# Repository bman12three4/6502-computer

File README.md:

# 65C02 Computer

My very own 65C02 computer.

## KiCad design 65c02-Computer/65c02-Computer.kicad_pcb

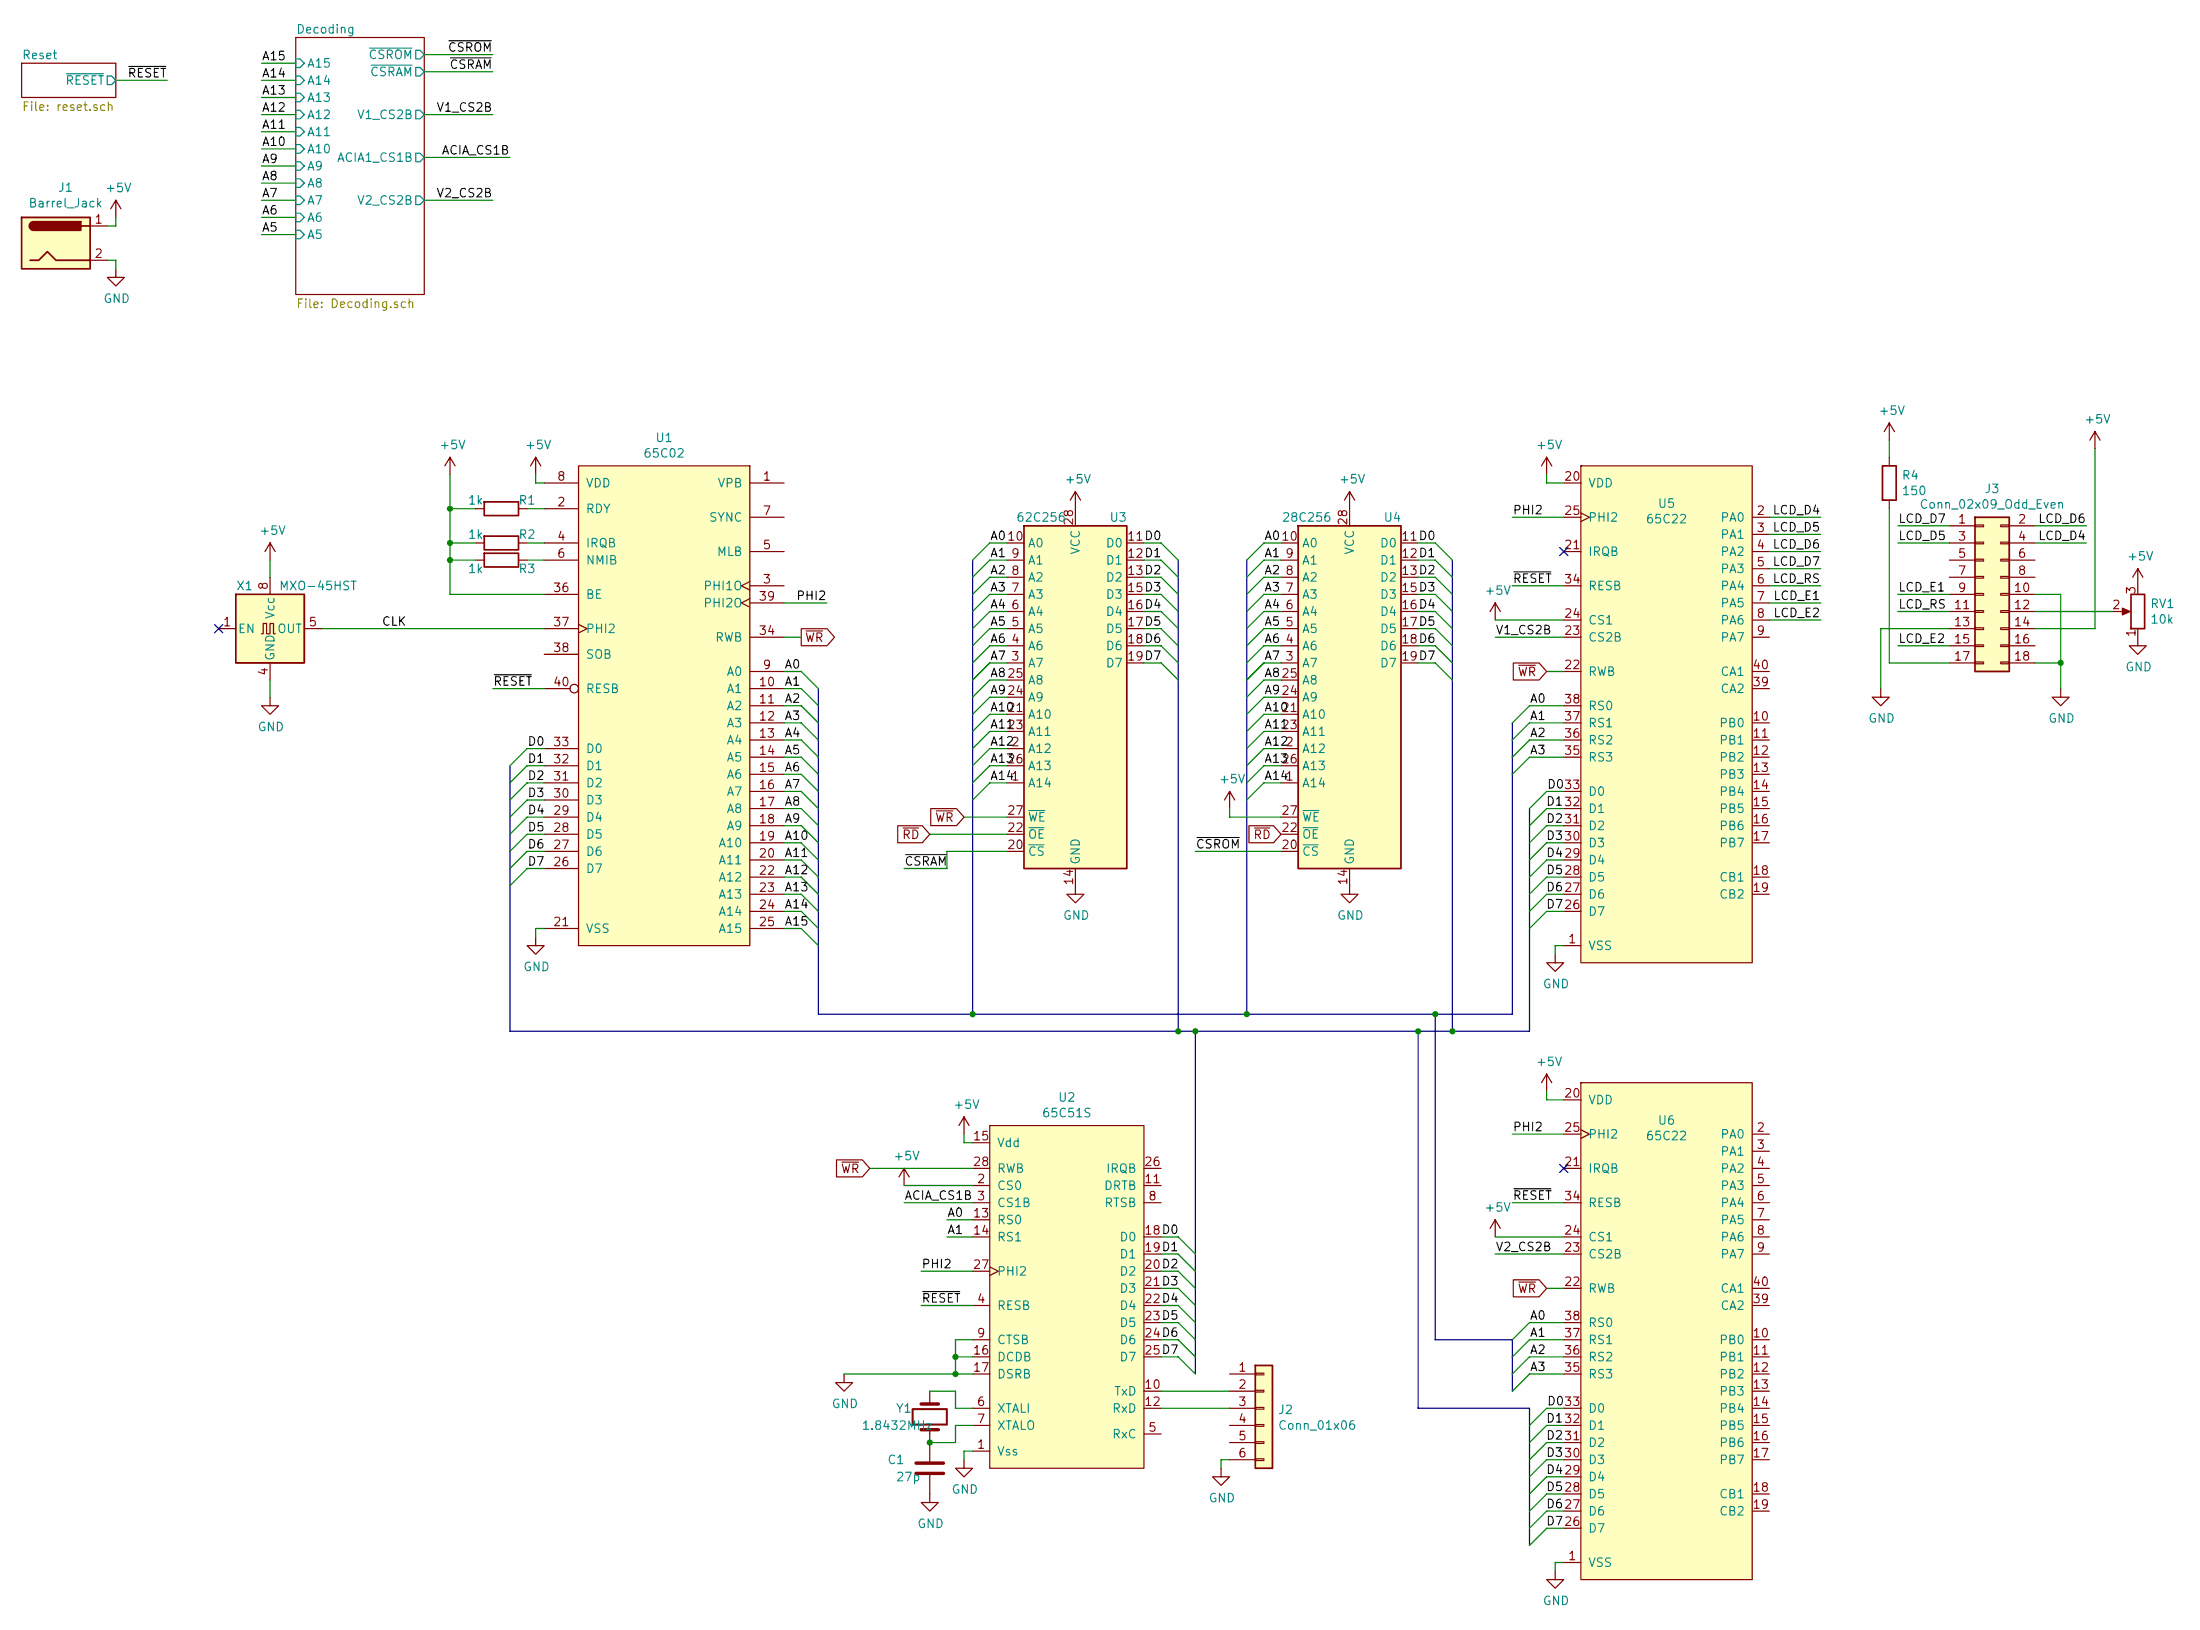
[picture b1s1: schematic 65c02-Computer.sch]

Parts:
C1: 27p; C_Disc_D3.8mm_W2.6mm_P2.50mm
J1: Barrel_Jack; BarrelJack_CUI_PJ-102AH_Horizontal
J2: Conn_01x06; PinSocket_1x06_P2.54mm_Horizontal
J3: Conn_02x09_Odd_Even; PinHeader_2x09_P2.54mm_Vertical
R1, R2, R3: 1k; R_Axial_DIN0207_L6.3mm_D2.5mm_P10.16mm_Horizontal
R4: 150; R_Axial_DIN0207_L6.3mm_D2.5mm_P10.16mm_Horizontal
RV1: 10k; PinHeader_1x03_P2.54mm_Vertical
U1: 65C02; DIP-40_W15.24mm_Socket_LongPads
U2: 65C51S; DIP-28_W15.24mm_Socket_LongPads
U3: 62C256; DIP-28_W15.24mm_Socket_LongPads
U4: 28C256; DIP-28_W15.24mm_Socket_LongPads
U5, U6: 65C22; DIP-40_W15.24mm_Socket_LongPads
X1: MXO-45HST; Oscillator_DIP-8
Y1: 1.8432MHz; Crystal_HC49-U_Vertical

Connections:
+5V: J1.1, J3.14, R1.2, R2.2, R3.2, R4.1, RV1.3, U1.8 (VDD), U1.36 (BE), U2.2 (CS0), U2.15 (Vdd), U3.28 (VCC), U4.27 (~WE), U4.28 (VCC), U5.20 (VDD), U5.24 (CS1), U6.20 (VDD), U6.24 (CS1), X1.8 (Vcc); also elsewhere on the board
/A0: U1.9 (A0), U2.13 (RS0), U3.10 (A0), U4.10 (A0), U5.38 (RS0), U6.38 (RS0)
/A1: U1.10 (A1), U2.14 (RS1), U3.9 (A1), U4.9 (A1), U5.37 (RS1), U6.37 (RS1)
/A2: U1.11 (A2), U3.8 (A2), U4.8 (A2), U5.36 (RS2), U6.36 (RS2)
/A3: U1.12 (A3), U3.7 (A3), U4.7 (A3), U5.35 (RS3), U6.35 (RS3)
/A4: U1.13 (A4), U3.6 (A4), U4.6 (A4)
/A5: U1.14 (A5), U3.5 (A5), U4.5 (A5); also elsewhere on the board
/A6: U1.15 (A6), U3.4 (A6), U4.4 (A6); also elsewhere on the board
/A7: U1.16 (A7), U3.3 (A7), U4.3 (A7); also elsewhere on the board
/A8: U1.17 (A8), U3.25 (A8), U4.25 (A8); also elsewhere on the board
/A9: U1.18 (A9), U3.24 (A9), U4.24 (A9); also elsewhere on the board
/A10: U1.19 (A10), U3.21 (A10), U4.21 (A10); also elsewhere on the board
/A11: U1.20 (A11), U3.23 (A11), U4.23 (A11); also elsewhere on the board
/A12: U1.22 (A12), U3.2 (A12), U4.2 (A12); also elsewhere on the board
/A13: U1.23 (A13), U3.26 (A13), U4.26 (A13); also elsewhere on the board
/A14: U1.24 (A14), U3.1 (A14), U4.1 (A14); also elsewhere on the board
/A15: U1.25 (A15), U3.20 (~CS); also elsewhere on the board
/ACIA_CS1B: U2.3 (CS1B); also elsewhere on the board
/CLK: U1.37 (PHI2), X1.5 (OUT)
/D0: U1.33 (D0), U2.18 (D0), U3.11 (D0), U4.11 (D0), U5.33 (D0), U6.33 (D0)
/D1: U1.32 (D1), U2.19 (D1), U3.12 (D1), U4.12 (D1), U5.32 (D1), U6.32 (D1)
/D2: U1.31 (D2), U2.20 (D2), U3.13 (D2), U4.13 (D2), U5.31 (D2), U6.31 (D2)
/D3: U1.30 (D3), U2.21 (D3), U3.15 (D3), U4.15 (D3), U5.30 (D3), U6.30 (D3)
/D4: U1.29 (D4), U2.22 (D4), U3.16 (D4), U4.16 (D4), U5.29 (D4), U6.29 (D4)
/D5: U1.28 (D5), U2.23 (D5), U3.17 (D5), U4.17 (D5), U5.28 (D5), U6.28 (D5)
/D6: U1.27 (D6), U2.24 (D6), U3.18 (D6), U4.18 (D6), U5.27 (D6), U6.27 (D6)
/D7: U1.26 (D7), U2.25 (D7), U3.19 (D7), U4.19 (D7), U5.26 (D7), U6.26 (D7)
/LCD_D4: J3.4, U5.2 (PA0)
/LCD_D5: J3.3, U5.3 (PA1)
/LCD_D6: J3.2, U5.4 (PA2)
/LCD_D7: J3.1, U5.5 (PA3)
/LCD_E1: J3.9, U5.7 (PA5)
/LCD_E2: J3.15, U5.8 (PA6)
/LCD_RS: J3.11, U5.6 (PA4)
/PHI2: U1.39 (PHI2O), U2.27 (PHI2), U5.25 (PHI2), U6.25 (PHI2)
/V1_CS2B: U5.23 (CS2B); also elsewhere on the board
/V2_CS2B: U6.23 (CS2B); also elsewhere on the board
/~CSROM: U4.20 (~CS); also elsewhere on the board
/~RESET: U1.40 (RESB), U2.4 (RESB), U5.34 (RESB), U6.34 (RESB); also elsewhere on the board
GND: C1.2, J1.2, J2.6, J3.10, J3.13, J3.18, RV1.1, U1.21 (VSS), U2.1 (Vss), U2.9 (CTSB), U2.16 (DCDB), U2.17 (DSRB), U3.14 (GND), U4.14 (GND), U5.1 (VSS), U6.1 (VSS), X1.4 (GND); also elsewhere on the board
unnamed: C1.1, U2.7 (XTALO), Y1.1
unnamed: J2.2, U2.10 (TxD)
unnamed: J2.3, U2.12 (RxD)
unnamed: J3.12, RV1.2
unnamed: J3.17, R4.2
unnamed: R1.1, U1.2 (RDY)
unnamed: R2.1, U1.4 (IRQB)
unnamed: R3.1, U1.6 (NMIB)
unnamed: U2.6 (XTALI), Y1.2
~RD: U3.22 (~OE), U4.22 (~OE); also elsewhere on the board
~WR: U1.34 (RWB), U2.28 (RWB), U3.27 (~WE), U5.22 (RWB), U6.22 (RWB); also elsewhere on the board

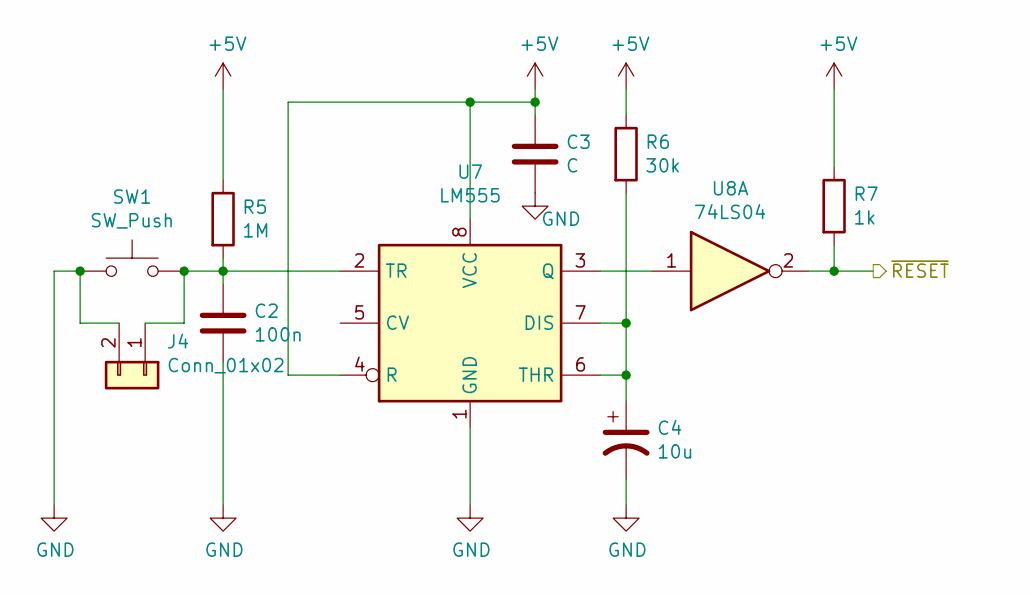
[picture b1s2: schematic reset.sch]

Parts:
C2: 100n; C_Disc_D3.8mm_W2.6mm_P2.50mm
C3: C; C_Disc_D3.8mm_W2.6mm_P2.50mm
C4: 10u; CP_Radial_D8.0mm_P5.00mm
J4: Conn_01x02; PinHeader_1x02_P2.54mm_Vertical
R5: 1M; R_Axial_DIN0207_L6.3mm_D2.5mm_P10.16mm_Horizontal
R6: 30k; R_Axial_DIN0207_L6.3mm_D2.5mm_P10.16mm_Horizontal
R7: 1k; R_Axial_DIN0207_L6.3mm_D2.5mm_P10.16mm_Horizontal
SW1: SW_Push; SW_PUSH_6mm_H4.3mm
U7: LM555; DIP-8_W7.62mm
U8: 74LS04; DIP-14_W7.62mm

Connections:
+5V: C3.1, R5.1, R6.1, R7.1, U7.4 (R), U7.8 (VCC); also elsewhere on the board
/~RESET: R7.2, U8.2; also elsewhere on the board
GND: C2.2, C3.2, C4.2, J4.2, SW1.1, U7.1 (GND); also elsewhere on the board
unnamed: C2.1, J4.1, R5.2, SW1.2, U7.2 (TR)
unnamed: C4.1, R6.2, U7.6 (THR), U7.7 (DIS)
unnamed: U7.3 (Q), U8.1

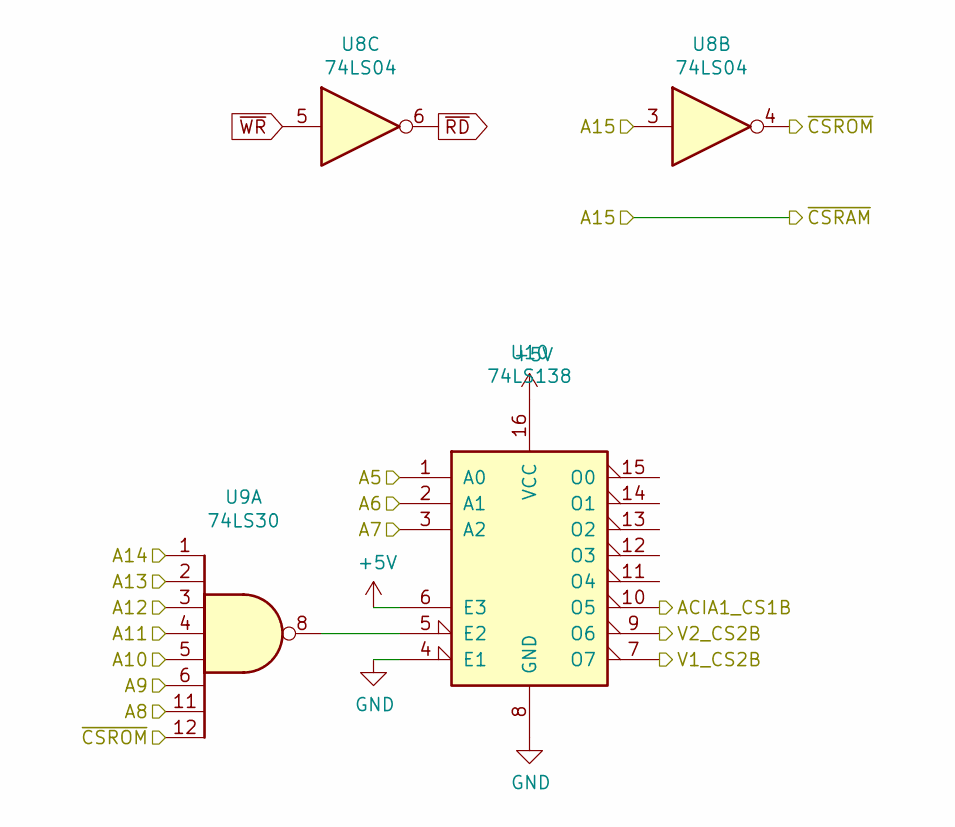
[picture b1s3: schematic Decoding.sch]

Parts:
U8: 74LS04; DIP-14_W7.62mm
U9: 74LS30; DIP-14_W7.62mm_LongPads
U10: 74LS138; DIP-16_W7.62mm_LongPads

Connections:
+5V: U10.6 (E3), U10.16 (VCC); also elsewhere on the board
/A5: U10.1 (A0); also elsewhere on the board
/A6: U10.2 (A1); also elsewhere on the board
/A7: U10.3 (A2); also elsewhere on the board
/A8: U9.11; also elsewhere on the board
/A9: U9.6; also elsewhere on the board
/A10: U9.5; also elsewhere on the board
/A11: U9.4; also elsewhere on the board
/A12: U9.3; also elsewhere on the board
/A13: U9.2; also elsewhere on the board
/A14: U9.1; also elsewhere on the board
/A15: U8.3; also elsewhere on the board
/ACIA_CS1B: U10.10 (O5); also elsewhere on the board
/V1_CS2B: U10.7 (O7); also elsewhere on the board
/V2_CS2B: U10.9 (O6); also elsewhere on the board
/~CSROM: U8.4, U9.12; also elsewhere on the board
GND: U10.4 (E1), U10.8 (GND); also elsewhere on the board
unnamed: U9.8, U10.5 (E2)
~RD: U8.6; also elsewhere on the board
~WR: U8.5; also elsewhere on the board

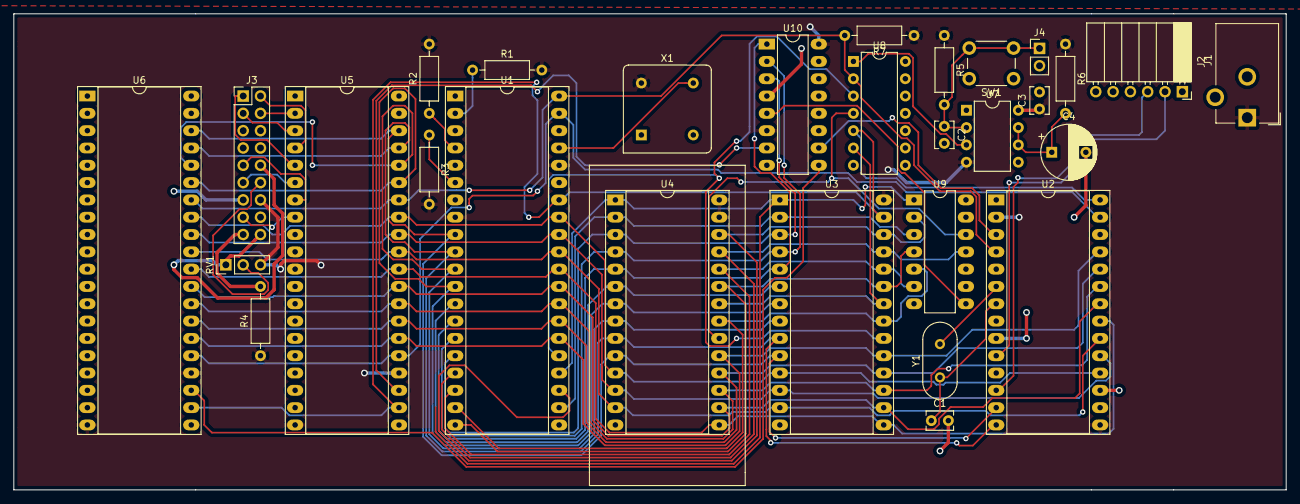
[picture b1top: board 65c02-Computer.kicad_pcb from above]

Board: 2 copper layers, 186.7 x 69.9 mm, 29 parts (0 on the bottom side), 55 nets.

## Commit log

2019-11-03 Create project and the main ICs
2019-11-03 Update library
2019-11-03 Create basic circuit
2019-11-03 Add firmware stuff and save schematic as a pdf
2019-11-06 Update symbols
2019-11-06 Connected VIA
2019-11-06 Rename clock signals and add annotations
2019-11-08 Add firmware and utilities
2019-11-08 Add gitignore, remove schedule app, not sure why that was in there
2019-11-14 Testing ram
2019-11-14 Update pcb and put arduino sketch
2019-11-16 Create v2
2019-11-17 Automated programming
2019-11-17 Removed unused 'iter'
2019-11-20 Switch to Make
